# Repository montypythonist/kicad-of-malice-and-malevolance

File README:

# happy birthday or something like that

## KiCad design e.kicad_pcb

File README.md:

# happy birthday or something like that

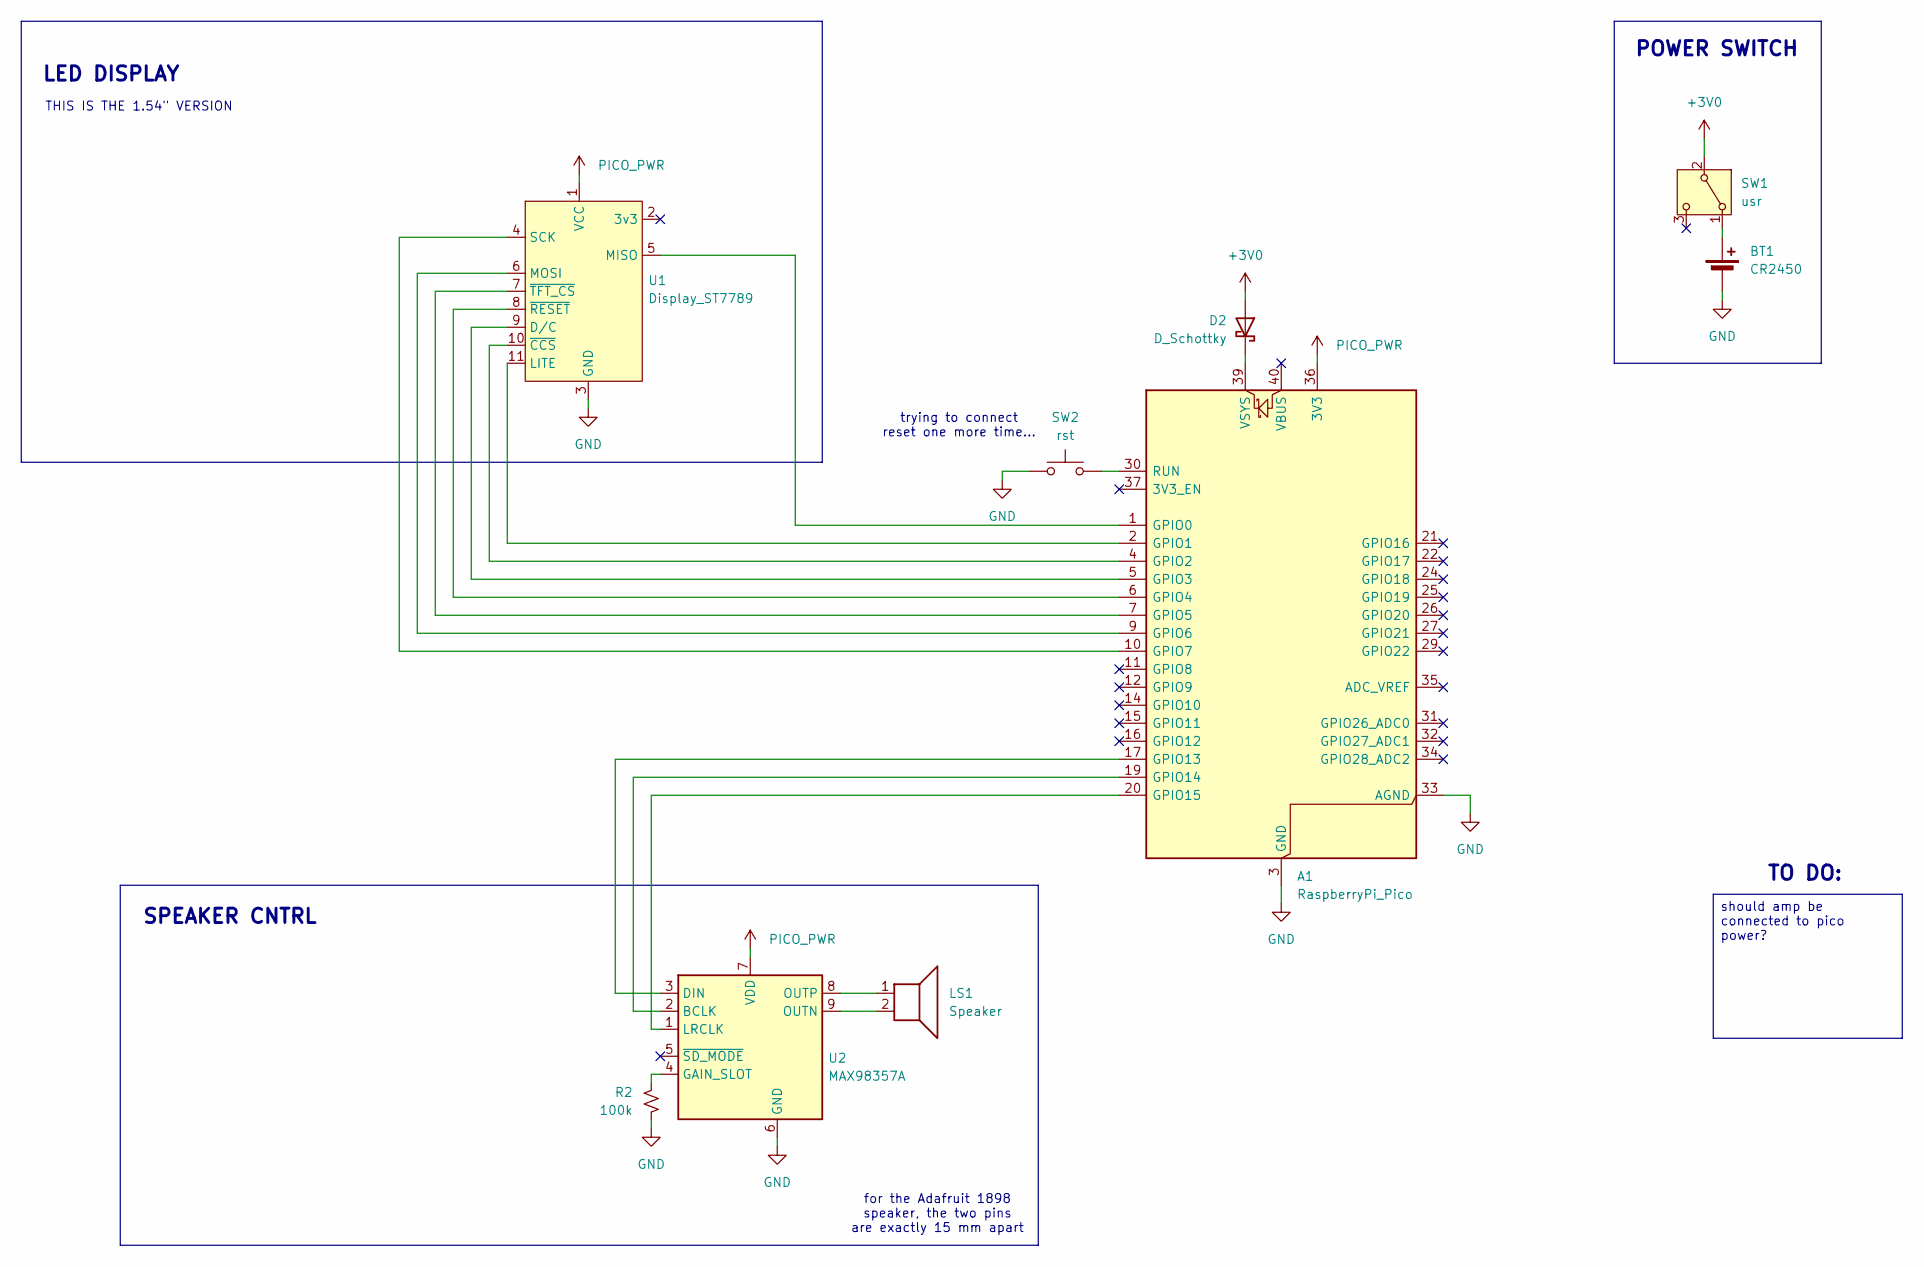
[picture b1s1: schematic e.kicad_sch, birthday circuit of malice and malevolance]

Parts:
A1: RaspberryPi_Pico; RaspberryPi_Pico_Common_SMD
BT1: CR2450; BatteryHolder_Keystone_3008_1x2450
D2: D_Schottky; D_SOD-128
LS1: Speaker; stupid-dumb-speaker
R2: 100k; R_Axial_DIN0207_L6.3mm_D2.5mm_P10.16mm_Horizontal
SW1: usr; SW_Slide_SPDT_Straight_CK_OS102011MS2Q
SW2: rst; SW_PUSH_6mm
U1: Display_ST7789; display-lol
U2: MAX98357A

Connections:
+3V0: D2.2 (A), SW1.2 (B)
GND: A1.3 (GND), A1.8 (GND), A1.13 (GND), A1.18 (GND), A1.23 (GND), A1.28 (GND), A1.33 (AGND), A1.38 (GND), BT1.2 (-), R2.2, SW2.1, U1.3 (GND), U2.6 (GND)
unnamed: A1.1 (GPIO0), U1.5 (MISO)
unnamed: A1.2 (GPIO1), U1.11 (LITE)
unnamed: A1.4 (GPIO2), U1.10 (~CCS)
unnamed: A1.5 (GPIO3), U1.9 (D/C)
unnamed: A1.6 (GPIO4), U1.8 (~RESET)
unnamed: A1.7 (GPIO5), U1.7 (~TFT_CS)
unnamed: A1.9 (GPIO6), U1.6 (MOSI)
unnamed: A1.10 (GPIO7), U1.4 (SCK)
unnamed: A1.17 (GPIO13), U2.3 (DIN)
unnamed: A1.19 (GPIO14), U2.2 (BCLK)
unnamed: A1.20 (GPIO15), U2.1 (LRCLK)
unnamed: A1.30 (RUN), SW2.2
unnamed: A1.39 (VSYS), D2.1 (K)
unnamed: BT1.1 (+), SW1.1 (A)
unnamed: R2.1, U2.4 (GAIN_SLOT)
unnamed: LS1.2, U2.9 (OUTN)
unnamed: LS1.1, U2.8 (OUTP)
PICO_PWR: A1.36 (3V3), U1.1 (VCC), U2.7 (VDD)

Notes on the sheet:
POWER SWITCH
TO DO:
SPEAKER CNTRL
LED DISPLAY
THIS IS THE 1.54" VERSION
for the Adafruit 1898 speaker, the two pins are exactly 15 mm apart
trying to connect reset one more time...
should amp be connected to pico power?

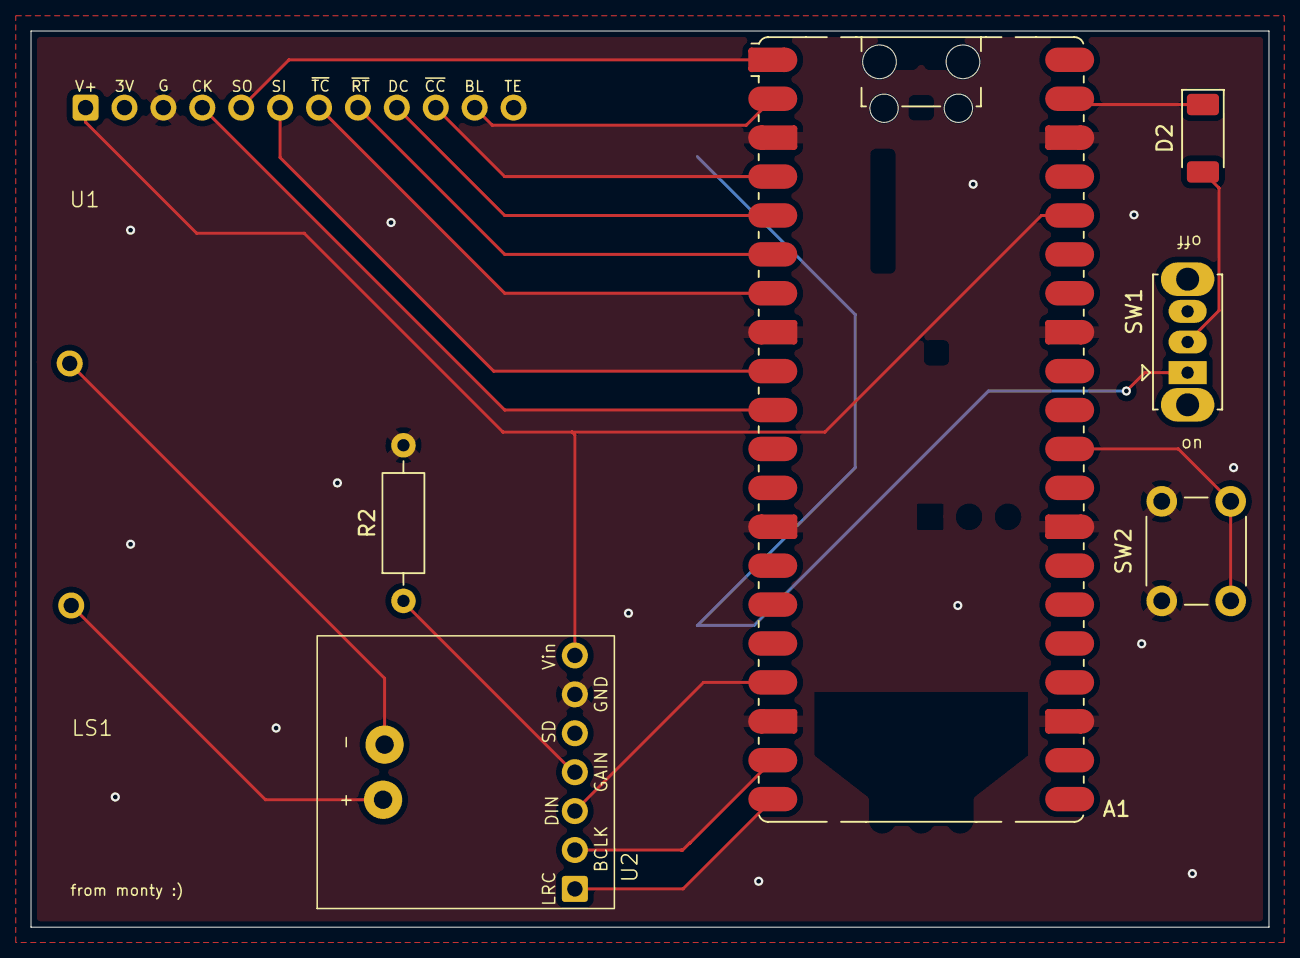
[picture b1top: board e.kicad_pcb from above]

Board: 2 copper layers, 80.8 x 58.5 mm, 9 parts (1 on the bottom side), 20 nets.

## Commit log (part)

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2026-05-22 init commit of doom!!
2026-05-29 forgot what i changed but it definitely changed
2026-06-01 cosmetic changes
2026-06-01 i have done it... the speaker has been wired! with only 36 errors from the ERC
2026-06-02 added a few footprints
2026-06-02 added datasheet links
2026-06-04 i did a thing
2026-06-05 i did MORE things
2026-06-05 its all doom and despair from here on out
2026-06-05 i rembered to put the ground plane this time trust
2026-06-05 omg yay pcb fully made and its amazing and beautiful and the DRC errors make no sense :3
2026-06-06 fixed so many things (i hope)
2026-06-07 new libraries and stuff
2026-06-07 Renamed custom footprint folder
2026-06-07 Updated footprint library path for custom footprints
2026-06-07 Updated footprints with more accurate pin sizing
2026-06-07 Updated footprints on PCB
2026-06-07 fixed some ERC/DRC errors
2026-06-10 wowwwww
2026-06-10 the board is smaller (but is it cheaper...?)
2026-06-11 the board is smaller... and cooler... and slightly cheaper!!
2026-06-12 almost done i hope
